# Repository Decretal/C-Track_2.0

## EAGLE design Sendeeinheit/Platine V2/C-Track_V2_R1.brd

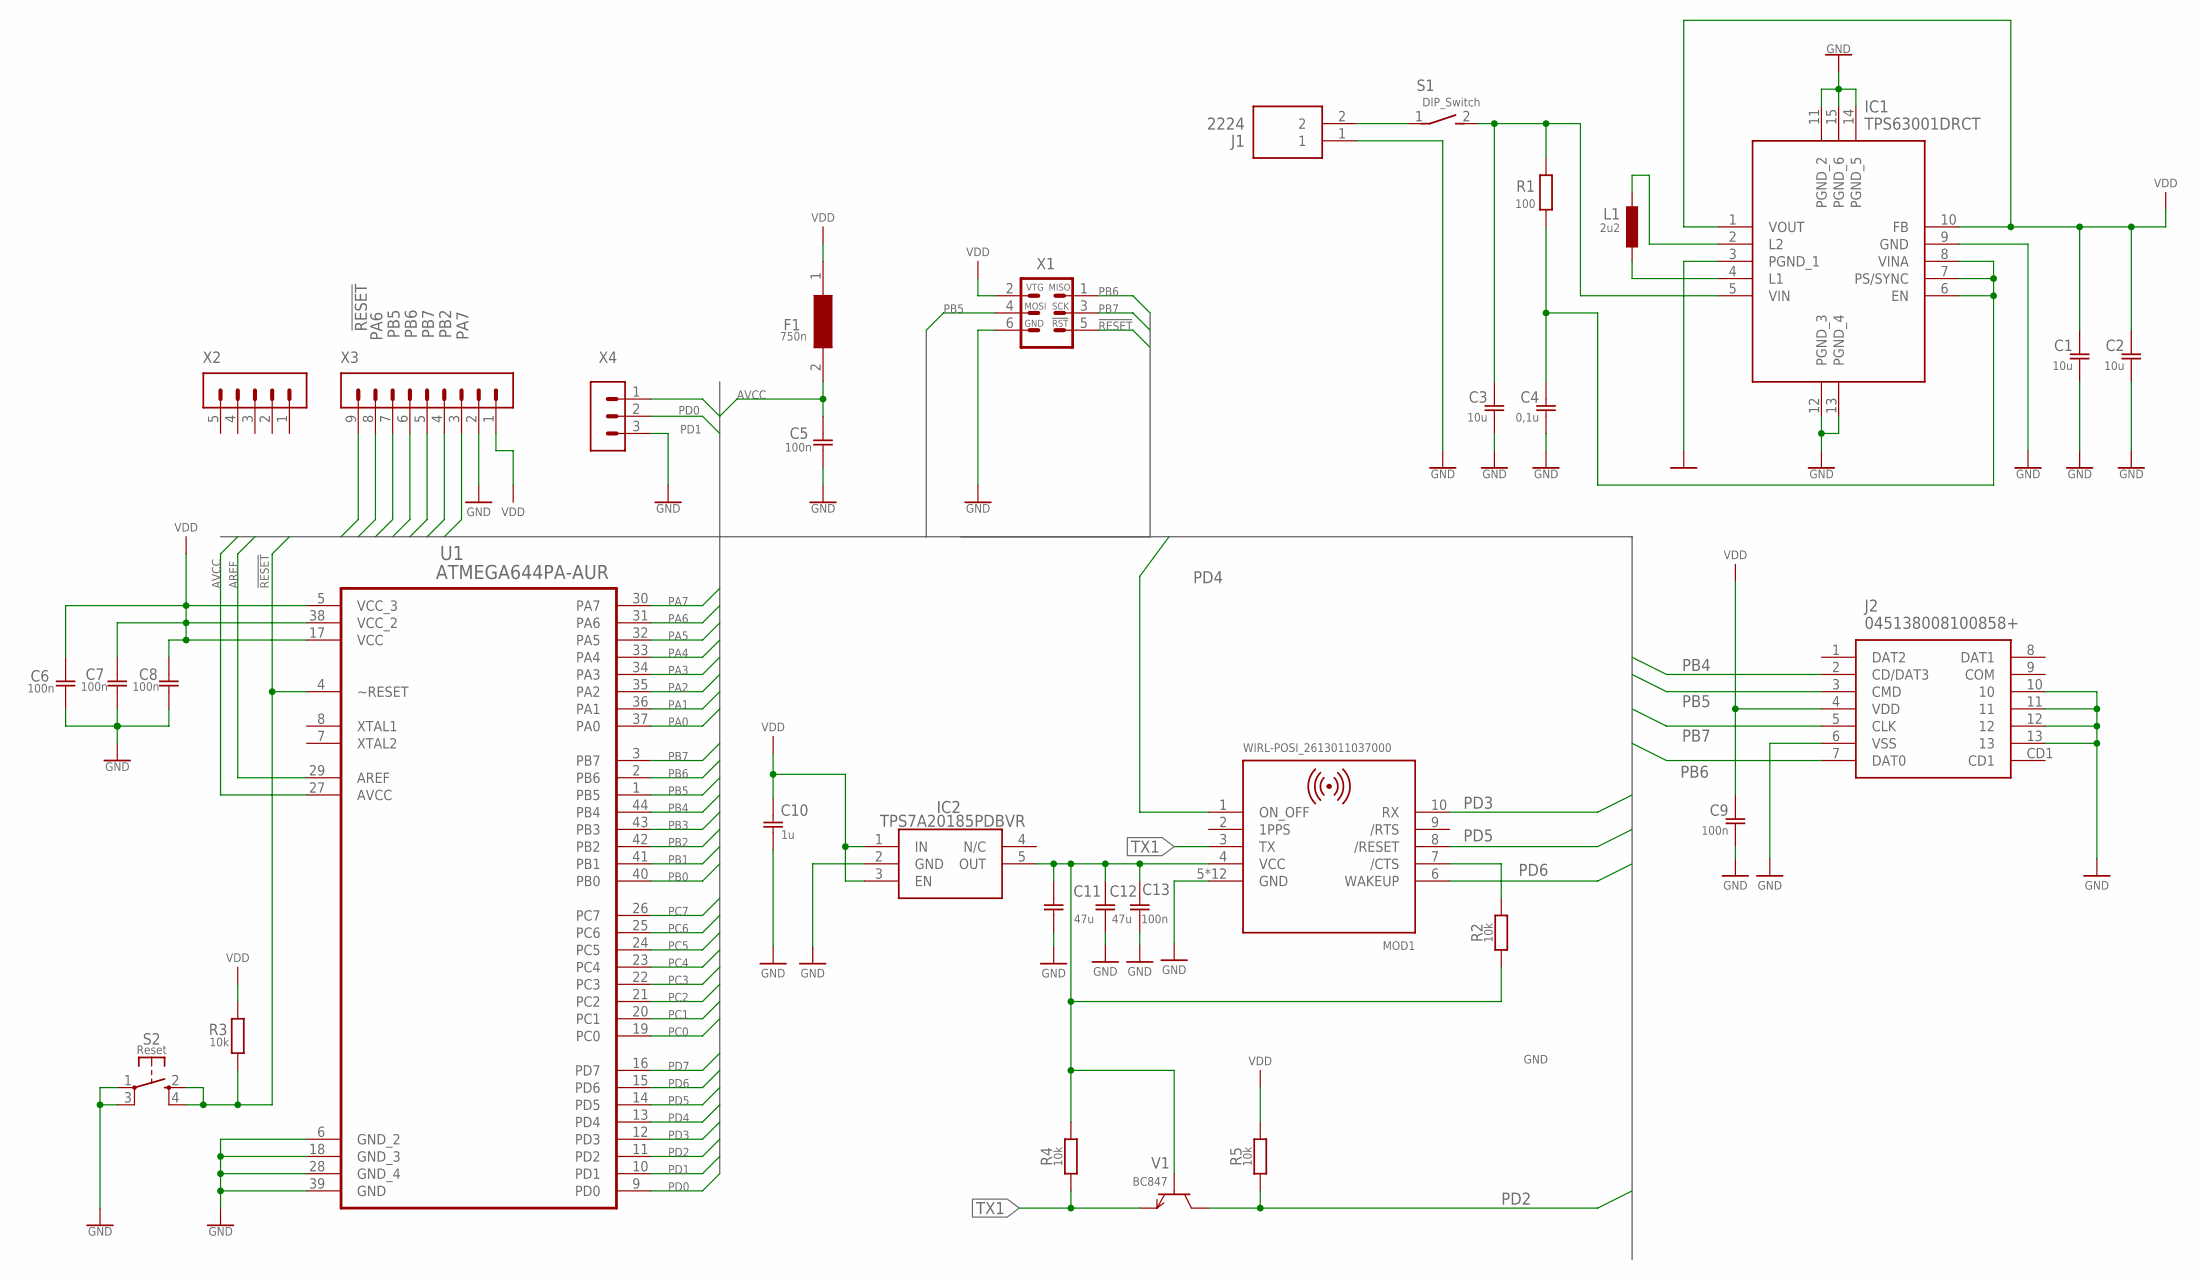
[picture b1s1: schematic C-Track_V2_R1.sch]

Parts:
C1, C2, C3: 10u; C0805
C4: 0,1u; C0805
C5, C6, C7, C8, C9, C13: 100n; C0805
C10: 1u; C0805
C11, C12: 47u; C0805
F1: 750n; SF1206HH1200R2
IC1: TPS63001DRCT
IC2: TPS7A20185PDBVR; SOT95P280X145-5N
J1: 2224
J2: 045138008100858+; 045138008100858
L1: 2u2; L0805
MOD1: WIRL-POSI_2613011037000
R1: 100; M0805
R2, R3, R4, R5: 10k; M0805
S1: DIP_Switch; DS04254201BKSMT
S2: Reset; WS-TASV-MICRO
U1: ATMEGA644PA-AUR; QFP80P1200X1200X120-44N
V1: BC847; SOT23
X1: MA03-2-
X2: MA05-1
X3: MA09-1MA-09-1; MA09-1
X4: MA03-1

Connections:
!RESET: R3.1, S2.2 (S), S2.4 (S1), U1.4 (~RESET), X1.5, X3.9 (8)
AREF: U1.29 (AREF)
AVCC: C5.1, F1.2, U1.27 (AVCC)
GND: C1.2, C2.2, C3.2, C4.2, C5.2, C6.2, C7.2, C8.2, C9.2, C10.2, C11.2, C12.2, C13.2, IC1.3 (PGND_1), IC1.9 (GND), IC1.11 (PGND_2), IC1.12 (PGND_3), IC1.13 (PGND_4), IC1.14 (PGND_5), IC1.15 (PGND_6), IC2.2 (GND), J1.1, J2.6 (VSS), J2.10, J2.11, J2.12, J2.13, MOD1.5 (GND), MOD1.P$1 (GND), MOD1.P$2 (GND), MOD1.P$3 (GND), MOD1.P$4 (GND), MOD1.P$5 (GND), MOD1.P$6 (GND), MOD1.P$7 (GND), MOD1.P$8 (GND), MOD1.P$9 (GND), MOD1.P$10 (GND), MOD1.P$11 (GND), S2.1, S2.3 (P1), U1.6 (GND_2), U1.18 (GND_3), U1.28 (GND_4), U1.39 (GND), X1.6, X3.2 (1), X4.3
unnamed: C3.1, IC1.5 (VIN), R1.2, S1.2
unnamed: IC1.4 (L1), L1.1
unnamed: C4.1, IC1.6 (EN), IC1.7 (PS/SYNC), IC1.8 (VINA), R1.1
unnamed: IC1.2 (L2), L1.2
unnamed: J1.2, S1.1
unnamed: C11.1, C12.1, C13.1, IC2.5 (OUT), MOD1.4 (VCC), R2.1, R4.2, V1.1 (B)
unnamed: MOD1.7 (/CTS), R2.2
PA0: U1.37 (PA0)
PA1: U1.36 (PA1)
PA2: U1.35 (PA2)
PA3: U1.34 (PA3)
PA4: U1.33 (PA4)
PA5: U1.32 (PA5)
PA6: U1.31 (PA6), X3.8 (7)
PA7: U1.30 (PA7), X3.3 (2)
PB0: U1.40 (PB0)
PB1: U1.41 (PB1)
PB2: U1.42 (PB2), X3.4 (3)
PB3: U1.43 (PB3)
PB4: J2.2 (CD/DAT3), U1.44 (PB4)
PB5: J2.3 (CMD), U1.1 (PB5), X1.4, X3.7 (6)
PB6: J2.7 (DAT0), U1.2 (PB6), X1.1, X3.6 (5)
PB7: J2.5 (CLK), U1.3 (PB7), X1.3, X3.5 (4)
PC0: U1.19 (PC0)
PC1: U1.20 (PC1)
PC2: U1.21 (PC2)
PC3: U1.22 (PC3)
PC4: U1.23 (PC4)
PC5: U1.24 (PC5)
PC6: U1.25 (PC6)
PC7: U1.26 (PC7)
PD0: U1.9 (PD0), X4.1
PD1: U1.10 (PD1), X4.2
PD2: R5.1, U1.11 (PD2), V1.3 (C)
PD3: MOD1.10 (RX), U1.12 (PD3)
PD4: MOD1.1 (ON_OFF), U1.13 (PD4)
PD5: MOD1.8 (/RESET), U1.14 (PD5)
PD6: MOD1.6 (WAKEUP), U1.15 (PD6)
PD7: U1.16 (PD7)
TX1: MOD1.3 (TX), R4.1, V1.2 (E)
VDD: C1.1, C2.1, C6.1, C7.1, C8.1, C9.1, C10.1, F1.1, IC1.1 (VOUT), IC1.10 (FB), IC2.1 (IN), IC2.3 (EN), J2.4 (VDD), R3.2, R5.2, U1.5 (VCC_3), U1.17 (VCC), U1.38 (VCC_2), X1.2, X3.1 (0)

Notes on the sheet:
MOSI
MISO
SCK
!RST
VTG
GND

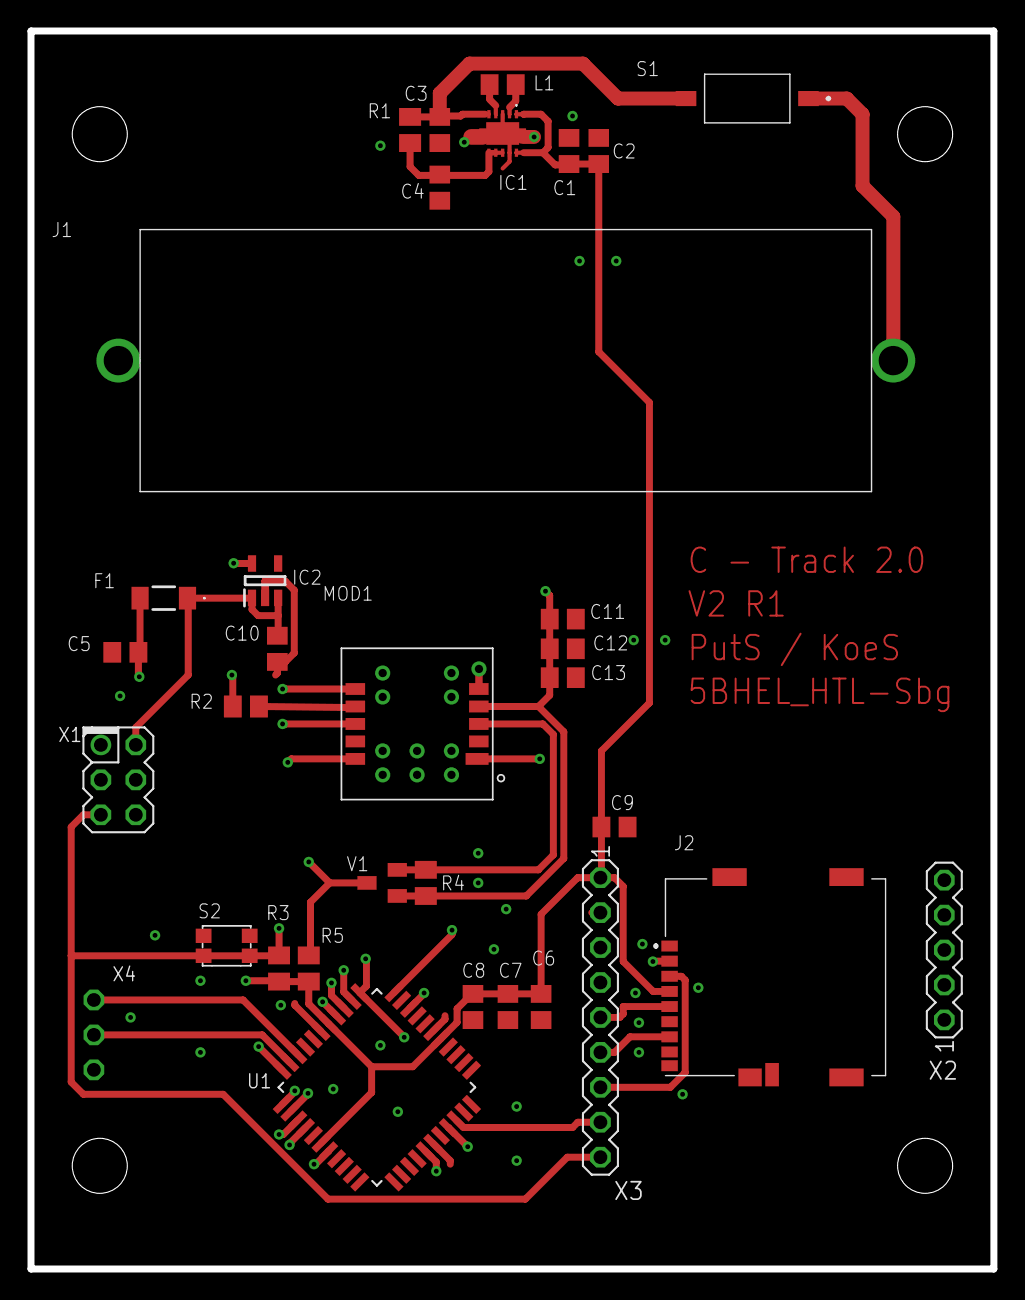
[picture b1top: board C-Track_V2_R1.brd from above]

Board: 4 copper layers, 70.0 x 90.0 mm, 33 parts (1 on the bottom side), 26 nets.

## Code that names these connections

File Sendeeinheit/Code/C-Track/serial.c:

/*
 * serial.c
 *
 * Created: 03.03.2024 14:45:52
 *  Author: Simon
 */ 


#include <avr/io.h>

/*
	SPI
*/

void spi_init()
{
	// Set MOSI (PB5), SCK (PB7), CSL (PA6) and CSSD (PB4) as outputs
	DDRB |= (1 << PB5) | (1 << PB7) | (1 << PB4);
	DDRA |= (1 << PA6);
	
	PORTA |= (1 << PA6);
	
	// Enable SPI, Set as Master, Set clock rate fck/4
	SPCR |= (1 << SPE) | (1 << MSTR) | (0 << SPR1) | (0 << SPR0);
}

void spi_tx(uint8_t dat)
{
	SPDR = dat;
	while(!(SPSR & (1<<SPIF)));
}

uint8_t spi_rx()
{
	SPDR = 0xFF;
	while(!(SPSR & (1<<SPIF)));
	return SPDR;
}

uint8_t spi_x(uint8_t data)
{
	SPDR = data;
	while(!(SPSR & (1<<SPIF)));
	return SPDR;
}


/*
	UART
*/

void uart_init()
{
	int ubrr = 12;
	// Set baud rate
	UBRR1H = (ubrr>>8);
	UBRR1L = ubrr;

	// Enable receiver and transmitter
	UCSR1B = (1<<RXEN1)|(1<<TXEN1);

	// Enable receive complete interrupt
	//UCSR1B |= (1 << RXCIE1);

	// Set frame format: 8 data, 1 stop bit
	UCSR1C = (1<<UCSZ11)|(1<<UCSZ10);
}


char uart_receive()
{
	// Wait for data to be received
	while (!(UCSR1A & (1 << RXC1)));
	// Return received data
	return UDR1;
}

void uart_transmit(char data)
{
	while (!(UCSR1A & (1 << UDRE1)));
	UDR1 = data;
}

void uart_sendStr(const char *data)
{
	while (*data != '\0')
	{
		uart_transmit(*data);
		data++;
	}
}

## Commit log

2024-04-15 init
2024-04-17 code
2024-04-18 alte apps gelöscht
2024-05-13 improved structure
2024-05-13 forgot something
2024-05-13 added 3D-Case
2024-05-17 cleanup
2024-05-18 Anleitung hinzugefügt
2024-05-20 dipl arbeit
2024-05-20 stuff
2024-06-04 App Instruction

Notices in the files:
parts and their libraries:
WE_WIRL_Rev10: Copyright: Würth Elektronik
